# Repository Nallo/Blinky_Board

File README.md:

# Blinky Board

EAGLE Project - Blinky Board

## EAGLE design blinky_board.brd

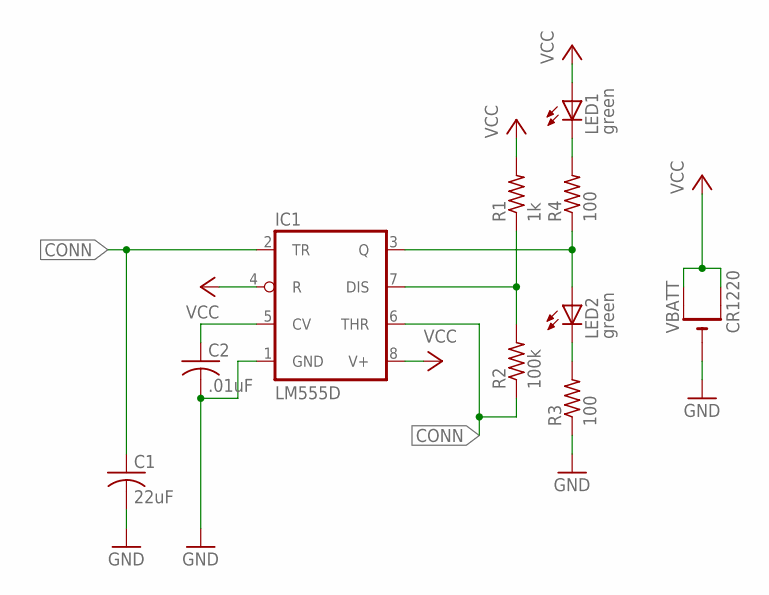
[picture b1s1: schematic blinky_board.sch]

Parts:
C1: 22uF; C0805
C2: .01uF; C0805
IC1: LM555D; SO08
LED1, LED2: green; CHIPLED_0805
R1: 1k; R0805
R2: 100k; R0805
R3, R4: 100; R0805
VBATT: CR1220; CR1220-SMD

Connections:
CONN: C1.1, IC1.2 (TR), IC1.6 (THR), R2.1
GND: C1.2, C2.2, IC1.1 (GND), R3.1, VBATT.-
unnamed: LED1.C, R4.2
unnamed: IC1.3 (Q), LED2.A, R4.1
unnamed: LED2.C, R3.2
unnamed: IC1.7 (DIS), R1.1, R2.2
unnamed: C2.1, IC1.5 (CV)
VCC: IC1.4 (R), IC1.8 (V+), LED1.A, R1.2, VBATT.+$1 (+), VBATT.+$2 (+1)

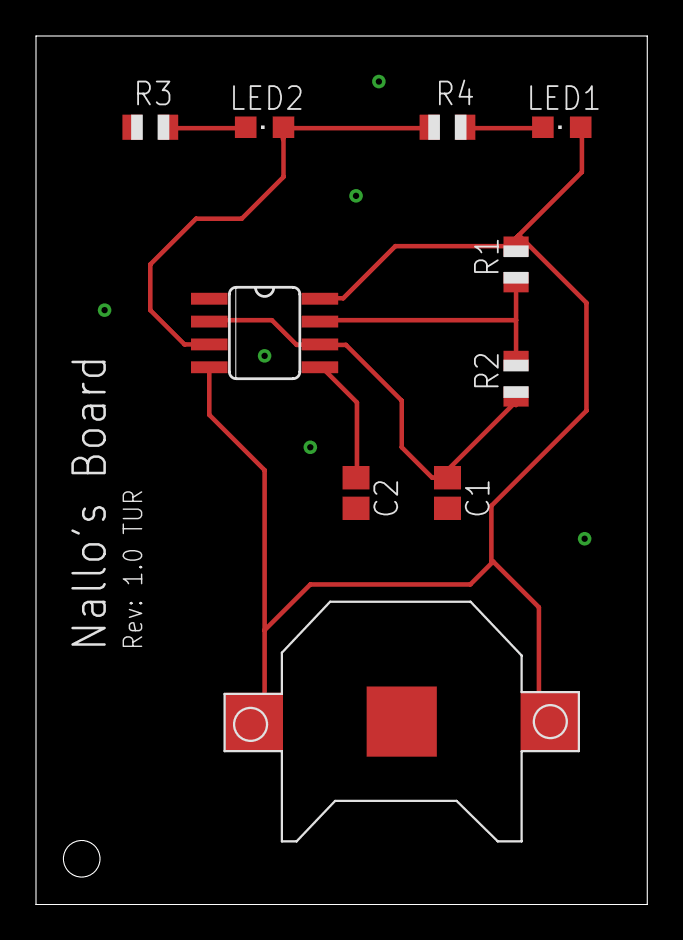
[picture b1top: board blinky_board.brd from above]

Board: 2 copper layers, 34.0 x 48.2 mm, 10 parts (0 on the bottom side), 8 nets.

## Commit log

2019-12-03 Board Rev 1.0 TUR
2019-12-04 Add BOM
2019-12-04 Add Gerbers
2019-12-04 Update BOM for single board
